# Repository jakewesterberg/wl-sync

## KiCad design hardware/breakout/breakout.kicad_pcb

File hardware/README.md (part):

# wl-sync breakout PCB

KiCad sources for the sync-box breakout board: a 2U rack-mount mixed-signal hub that sits
between the behavioural task PC, the sync-box module, the recording NI card, and the Intan RHS
amplifier. Every signal that crosses between those devices terminates on this board, is
conditioned once, and is fanned out — so a rig is reproducible from the board rather than from
hand wiring. "Sync-box module" is deliberately not a single product name: the module carries a
BCM2712 SoC and RP1 I/O controller either way, so its GPIO map and pinout are identical whether
it ships as a Raspberry Pi 5 or as a Compute Module 5 (Lite) on the official CM5 IO Board — the
choice between the two is a floorplan/placement decision this repository's own sources do not
yet lock in, not an electrical one.

Full design rationale, the signal contract, the grounding scheme, and the fabrication schedule
live in [`docs/superpowers/specs/2026-08-13-syncbox-breakout-pcb-design.md`](../docs/superpowers/specs/2026-08-13-syncbox-breakout-pcb-design.md).
The implementation plan (task breakdown, net naming convention, file layout) is at
[`docs/superpowers/plans/2026-08-13-breakout-pcb.md`](../docs/superpowers/plans/2026-08-13-breakout-pcb.md).
This repository is public: documentation here states electrical and mechanical facts and
tooling instructions only, and reproduces no text from either linked document's private source
material.

## Settled facts (record kept here, 2026-08-15)

Three facts a rig operator or firmware author needs and should not have to re-derive from the
schematic or the private spec:

- **The two photodiode comparator channels have distinct, fixed roles.** `A_PD1` watches the
  **task patch** — the stimulus-onset signal a behavioural task draws to cue an event.
  `A_PD2` watches the **flip patch**, a corner region of the display that alternates every
  refresh, making it a frame clock. Both reach the recorders as a digital edge through their
  own comparator (`PD1_COMP`/`PD2_COMP`) as well as an analog copy; the comparator lines carry
  the timing, the analog copies carry waveform and intensity.
- **The default eight analog channels Intan receives** (of the 16 sources this board carries;
  Intan's own ceiling is 8, and which eight is a mux setting, not a copper fact — see the
  ADG1206 mux truth table below): `A_PD1`, `A_EYE_LX`, `A_EYE_LY`, `A_EYE_LP`, `A_JOY_X`,
  `A_JOY_Y`, `A_MIC`, `A_ACC`. One complete eye (left, position + pupil) rather than partial
  data from both; the six eye channels are the first candidates to drop if a different set is
  ever needed, since they have an authoritative record on the eye-tracker PC independent of
  this board — the photodiode, joystick, accelerometer, and microphone channels do not.
- **MonkeyLogic's `RewardPolarity` setting must be `HIGH` to match this board.** This board's
  reward-commanded input (`RWD_CMD`) is active-HIGH by design (idle-LOW, pulses HIGH on
  delivery — the same convention every other event line on this board uses, and the polarity
  the reward-OR gate's own same-polarity structural check assumes and enforces on the
  debounced-button side). `RewardPolarity` is a MonkeyLogic Main Menu setting provided so a
  rig can match relays that trigger on sinking instead — it is a configuration to set for this
  board, never an unknown to discover at commissioning time.

## Two tracks

- **`hardware/mule/`** — the event-path mule. A small, fast board carrying only the 17-line
  event-code path plus one instance of each level-shift and isolation stage the full board
  reuses. It exists to reach the bench while the breakout board is still in layout, so the
  level-shifting and optocoupler topology gets validated against real hardware early enough to
  revise the sheets that depend on it.
- **`hardware/breakout/`** — the breakout board itself. A root sheet plus one hierarchical sheet
  per functional block (power, task-PC digital, Pi interface, analog front end, analog-to-NI,
  mux-to-Intan, comparators, opto-to-NI, opto-to-Intan, USB/I²C control).

**To route the breakout board, start at `hardware/breakout/routing-brief.md`** (2026-11-21).
The placement is generated and merged, and the brief is the handoff to the person who
routes it: what to open, what must not move, the net classes, the order to route in, the
rules by ID, the checks afterwards and what is still open. It cites the documents below
and changes none of their rules.

**Before laying out the breakout board, read `hardware/breakout/constraints.md`.** It is the
layout constraint set for plan Task 14: ground domains and the four net ties, the isolation
barriers and their slot margins, net classes, sensitive-net placement, keep-outs and the
connector faces. Every rule in it cites its source or is marked as engineering judgment, and
it ends with the questions the designer still has to answer. It sits beside the documents it
draws on: `design-review.md` (the sign-off that gates layout), `parametric-audit.md`,
`panel-elevations.md`, `frame-time-inputs.md`, `line-out-and-pfi-copy.md` and
`f6-review-brief.md`.

As of this commit, `hardware/mule/` carries a generated schematic (`mule.kicad_sch`, produced
by `hardware/gen/gen_mule.py`) and a generated, placed-but-unrouted board (`mule.kicad_pcb`,
produced by `hardware/gen/gen_mule_pcb.py`) — see `hardware/mule/floorplan.md` for the
placement rationale and the constraints a router must respect. `hardware/breakout/` carries
the root sheet (`breakout.kicad_sch`, produced by `hardware/gen/gen_breakout.py`) plus two
populated child sheets so far: `sheets/power.kicad_sch` (produced by
`hardware/gen/gen_breakout_power.py`, Task 7) — the 5-position analog/logic inlet (widened
from 4 pins at Task 7 fix round 1, see below), the +3V3 logic rail regulated from +5V, and
the one isolated ±12V supply the other nine sheets draw power from; see that generator's own
module docstring and `check_breakout_power_netlist.py` for the design and its verification.
Task 7 fix round 1 (task-7-report.md's "Fix round 1") corrected two defects found in
review: the +5V rail was undersized regulating it down from +12V on board (fixed by
bringing +5V in directly from the external supply on a fifth inlet pin instead, budgeted
for 400mA), and the child sheet's own component `(instances (path ...))` ancestor chain was
self-referential rather than the real root+sheet-symbol chain a nested sheet needs (fixed
generically in `kicad_sch.py`, not just for this one sheet — see the "KiCad gotchas" entry
below). Task 7 fix round 2 (task-7-report.md's "Fix round 2") replaced the inlet
**connector** itself — not its electrical design — after a reviewer confirmed the mini-DIN
footprints modelled an evenly-spaced ring the real Same Sky MD-40SN/MD-50SN datasheet's own
diagrams contradict, and that both parts are discontinued besides. The inlet is now a
5-position, IEC 61076-2-101 A-coded, keyed, screw-locking M12 connector (Amphenol LTW
M12A-05PFFP-SF8001, current production, 811 units in stock directly confirmed at DigiKey)
— see "Custom connector footprints" below for the full selection rationale and
per-dimension sourcing.

**Panel-instrumentation task (2026-08-15), Change D — four of the five "things a rack
instrument needs that this one lacked" (spec §9.8) land on this sheet** (the fifth,
the barcode heartbeat LED, is on `pi-interface.kicad_sch` — see that sheet's own
paragraph below):

- **Chassis earth stud (`J56`):** a `Connector_Generic:Conn_01x01` on footprint
  `MountingHole:MountingHole_3.2mm_M3_Pad` — an M3-clearance hole *with* a connected
  copper pad, simultaneously the mechanical mount and the electrical land the
  cage-to-rack bond (spec §5.6) needs somewhere to terminate. Carries a new net,
  `CHASSIS_GND`, joined to `DGND` at exactly one net tie (`NT3`) — mirroring `NT2`'s own
  `FAN_RTN`↔`DGND` treatment exactly, so the stud reaches the board's single star point
  transitively (through `NT3` then `NT1`/`NT2`), never by a second, competing path.
- **Power-good LED per rail (`D40`/`D41`/`D42`, +12V/−12V/+5V):** series resistor + LED
  between each rail and its own local ground reference (`AGND` for ±12V, `DGND` for
  +5V) — `−12V`'s own pair is mirrored (resistor/anode on the `AGND` side, cathode on
  `−12V`), the identical reasoning `D2`'s own reverse-polarity-diode orientation already
  uses. ~4.5 mA target each (`R192`/`R193` = 2.2k, `R194` = 680R) — negligible against
  any rail's own real budget.
- **Rail test points (`TP1`–`TP7`):** one `Connector:TestPoint` per voltage rail (+12V,
  −12V, +5V, +3V3, ISO_P12, ISO_N12) *plus one on `INTAN_GND`* — the isolated domain's
  own reference, without which `ISO_P12`/`ISO_N12` cannot actually be measured at all
  (`INTAN_GND` is galvanically separate from `AGND`/`DGND`, spec §5.3/§5.5). `AGND`/
  `DGND` themselves are not given dedicated test points — already trivially probable at
  any of this sheet's own many ground pads.
- **Main input fusing (`F2`/`F3`/`F4`, +12V/−12V/+5V):** "the fans already have a
  polyfuse; these did not" (spec §9.8). Placed upstream of each rail's own existing
  reverse-polarity diode (`D1`/`D2`/`D3`) — their own raw-side net renamed `*_FUSED`
  (e.g. `P12_RAW` → `F2` → `P12_FUSED` → `D1` → `+12V`), `D1`–`D3` themselves keeping
  their existing references unchanged. `F2`/`F3` are Littelfuse `1206L050/15YR`
  (500 mA hold / 1 A trip / **15 V** max), the same real part as the fan feed's `F1`.

  **`F4` is a different part — finding M7, 2026-08-16.** The sizing note that used to
  sit here called +5V's 1.25× hold margin "tighter than usual but accepted, because a
  main-input fuse guards against a gross fault". That reasoning does not survive finding
  F1: the +5 V rail now carries **392 mA typ / 495 mA max**, and a `1206L050` holds only
  ~0.44 A at this chassis's 35 °C ambient. It would have tripped in **normal operation**,
  not on a fault. `F4` is now **`1206L110-C`** — 1.10 A hold / 2.20 A trip, ~0.97 A
  derated at 35 °C, a 1.97× margin.

  **Its V_max is 6 Vdc, not 15, and that is not interchangeable.** In the 1206L series
  the elevated-voltage variants exist only at the two lowest hold currents; everything at
  0.75 A and above is a +5 V-rail part. So `F4` could move and `F1`/`F2`/`F3` cannot —
  **0.50 A is the largest 1206L hold current available to a 12 V rail at all**, which is
  also why M7's "0.75 A recommended" for the fan feed cannot be satisfied in this series.
  Do not consolidate the two values back into one.

- **The fan branch is parallel to the main +12 V branch, not downstream of it (finding
  F7, 2026-08-16).** `F1` used to be fed from `+12V`, which put it in series with `F2` at
  identical ratings — and two identical parts in series have no selectivity at all: a fan
  fault at 0.9 A is below `F1`'s trip but over `F2`'s hold, so **`F2` could open first and
  kill the analog rails to protect the fans.** The fan feed now taps `P12_RAW` directly,
  with its own reverse-polarity Schottky (`D44`, `SS14`) since it no longer sits behind
  `D1`:

  ```
  J1.1 → P12_RAW ─┬─ [F2] → P12_FUSED   → [D1]  → +12V      (main, 97–121 mA)
                  └─ [F1] → FAN_12V_RAW → [D44] → FAN_12V   (fans, 240 mA)
  ```

- **Every panel output now sits behind series resistance, and no logic output drives more
  than one connector (findings F4 and M3, 2026-08-16).** `CAM_TRIG_BEH` drove **four** BNCs
  from a single `SN74AHCT541` output: four parallel coax runs present Z₀/4 ≈ 12.5 Ω, so the
  initial edge drew roughly **118 mA against the part's 25 mA per-output absolute
  maximum** — brief, but on every edge for the life of the board, and with no source
  termination the cameras could see reflections and double-trigger. Each trigger now has its
  own buffer channel (`CAM_TRIG_BEH1`–`4`, the extra three on `U74`) and its own **47 Ω**.
  They still share one trigger *rate* via `CAM_TRIG_BEH_RAW`; they no longer share a driver.

  M3 named **six** bare panel outputs. There were **eleven** — the five *digital* Intan
  output BNCs sat directly on the ACSL-6xx0 output pins too. (The finding's "every Intan
  output has a series resistor" is true of the *analog* outputs, which each sit behind
  100 Ω, and was not true of the digital ones.) All eleven now carry series resistance:
  47 Ω on the five camera triggers, 100 Ω on `J6` and the five Intan BNCs. The extra five
  were found by the checker written *for* M3, which is stated over every panel output rather
  than over the six nets the finding lists.

  `tests/hardware/test_netlist.py` derives series-ness from **topology** — by testing
  whether removing one fuse disconnects another from the supply inlet — rather than from
  net names. That matters: the audit's own published fix for this named `P12_FUSED` as
  "upstream of `F2`" when it is `F2`'s *output*, which would have fixed nothing and
  removed the fan branch's reverse-polarity protection as well. ±12V's own real total draw was **not** independently characterized
  to the same precision (it sums a computed IH1215D input-current estimate, the fan
  feed, and an uncharacterized contribution from the ±12V-referenced op-amp stages on
  `analog-frontend.kicad_sch`/`analog-ni.kicad_sch`) — flagged explicitly for bench
  confirmation before treating the margin as final, the same "tell me if it doesn't fit"
  posture this file's own +3V3/NI-budget notes already use elsewhere. A higher-current,
  higher-voltage PPTC (Bourns `MF-SM` series) was evaluated and **rejected**: its own
  datasheet states hand soldering is not recommended, which would add a third accepted
  hand-solderability exception beyond the two spec §10.1 documents (`MCP4728`, the two
  exposed-pad regulators) — see `_place_inlet()`'s own docstring for the full account.

And `sheets/taskpc-digital.kicad_sch` (produced by
`hardware/gen/gen_breakout_taskpc_digital.py`, Task 8) — both task-PC MDR68 connectors
(Connector 1 wired with the 23 digital lines; Connector 0 carries its 9 task-PC analog
channels plus the AISENSE-to-AGND tie, everything else no_connect pending Task 10's own
front-end/buffer circuitry), the 19-channel inbound protected/buffered path (100Ω +
BAT54S clamp per channel, high side +5V never +3V3, fanned out in parallel to a 3.3V
`SN74LVC541APW` bank and a 5V `SN74AHCT541PW` `_BUF` bank for Task 11's optocouplers), the
4-channel outbound path, and the reward OR (`74HCT32` + a single debounced `74HCT14`
Schmitt inverter); see that generator's own module docstring and
`check_taskpc_digital_netlist.py` for the design and its verification. Task 8 is this
project's first case of two REAL sibling child sheets coexisting, which surfaced a
cross-sheet reference-collision gotcha `kicad_sch.py` needed a generic fix for — see the
"KiCad gotchas" entry below.

**Task 8 fix round 1** (`task-8-report.md`'s own "Fix round 1") corrected three findings
raised by the implementer's own report, all disclosed concerns the implementer was right
to flag: (1) **critical** — the reward-OR debounce stage placed a `74HCT14` Schmitt
*pair* (task-8-brief.md's own literal, incorrect text); two series inversions cancel, so
the debounced button would idle HIGH into an OR gate against an active-HIGH `RWD_CMD`,
asserting `RWD_DLVR` continuously. Fixed to a *single* inverter (idle-LOW/active-HIGH,
matching an OR gate's actual requirement); `RWD_CMD`'s assumed active-HIGH polarity is
now stated explicitly on-sheet, and the checker asserts the OR's two inputs are
same-polarity. (2) Connector 1's physical MDR68 pin assignment was this sheet's own
sequential guess; it is now sourced from NI's own "X Series User Manual" (National
Instruments 370784K-01, May 2019), Figure A-5 "NI PCIe-6323/6343 Pinout" — the task PC's
own card — for every P0.x and D GND position. (3) Connector 0's 9 task-PC analog channels
(`A_EYE_LX_TPC` etc., plan.md's own net-naming table) and its AISENSE-to-AGND tie are now
wired on this sheet (the same physical-pin source above), since only the file that places
a symbol can label its pins and Task 10 does not exist yet. See `task-8-report.md`'s own
"Fix round 1" section for the full retrieval/verification method and the reasoning behind
each fix.

**Panel-instrumentation task (2026-08-15), Changes A+B — manual reward becomes a one-shot,
and the three reward positions become real connectors.** Both changes land entirely on
`taskpc-digital.kicad_sch`'s own reward circuit:

- **One-shot (Change A):** a Nexperia `74HCT123D` dual retriggerable monostable (`U69`)
  now sits between the debounce inverter's own output (`RWD_BTN_DEB`) and the reward-OR
  gate's second input (`RWD_BTN_PULSE`, the one-shot's own `Q`) — every hand-delivered
  reward gets a fixed **~199 ms** pulse regardless of how long the button is held (spec
  §3.1). `Rext=442k` (E96) + `Cext=1µF` (`R191`/`C149`, both minted out of band), K=0.45 at
  VCC=5.0V (the part's own datasheet, Table 10) → tW = 0.45×442×1,000,000 ns ≈ 198.9 ms,
  cross-checked against that same table's own measured example (100 nF/10 kΩ → 450 µs;
  the formula predicts exactly that). Real part, not TI: TI's own `CD74HCT123M`/`MT` is
  obsolete; Nexperia's `74HCT123D` is current production, thousands of units in stock at
  DigiKey/Mouser/TME (checked 2026-08-15). Pin map verified pin-by-pin against
  Philips/Nexperia's own Rev. 03 (11 May 2004) datasheet, Table 3/Fig. 5, cross-checked
  against KiCad's own stock `74xx:74HCT123` library entry — see
  `gen_breakout_taskpc_digital.py`'s own `place_reward_oneshot()` docstring for the full
  account, including why the part's own retriggerable behaviour does not undermine "fixed
  duration regardless of hold time" (a continuous hold produces exactly one trigger edge).
  The debounce capacitor changes from 100 nF to **1 µF** (10 kΩ × 1 µF = 10 ms, spec
  §3.1), covering both switch bounce and the longer remote-BNC cable run's own
  connector-mating transient.
- **Real connectors (Change B):** the manual reward button (`J4`) is now
  `Switch:SW_Push` on a real panel/chassis-mount momentary-pushbutton footprint
  (`Button_Switch_THT:SW_PUSH-12mm`), **recessed** per spec §3.1 ("so a sleeve or cable
  cannot dispense fluid"). The remote reward jack (`J5`) and reward-driver output (`J6`)
  are both real BNCs (`Connector:Conn_Coaxial` / `Connector_Coaxial:BNC_PanelMountable_
  Vertical` — the same footprint the camera-trigger BNCs already use), replacing generic
  `Connector_Generic:Conn_01x02` placeholders. **This removes the 3.5 mm TRS from the
  design entirely** — `J5` was its last use (spec §9.6): a BNC's own center pin cannot
  transiently short to the shield while mating the way a TRS tip/ring/sleeve does sliding
  past a jack's own switching contacts, so plugging in the handheld remote cannot itself
  fire a reward, and the coupling locks. No TRS footprint or symbol exists anywhere on the
  board any more (confirmed by grep across every generator and committed sheet, and
  asserted directly by `check_taskpc_digital_netlist.py`'s own whole-board footprint scan,
  with a negative control). `J4`/`J5`/`J6` keep their existing reference numbers — the
  symbol/footprint/value changed at their own existing call sites, nothing moved.

**A real ref_start hazard, found and fixed while making these changes, not before:**
`taskpc-digital.kicad_sch`'s own `build()` used to re-derive its reference-counter seed by
reading `power.kicad_sch`'s *current* committed text on every regeneration
(`find_max_refs(POWER_SCH.read_text())`). That was safe until power.kicad_sch's own
fan-header addendum (spec §9.5) minted `J52`–`J55`/`C147`/`C148` out of band, *after*
taskpc-digital.kicad_sch was last generated — from that point on, simply regenerating
taskpc-digital.kicad_sch again (even with no source changes at all) would have silently
**renumbered every one of its own existing J- and C-prefixed components**, since the
recomputed seed jumps from the sheet's own small pre-fan-header baseline straight to
power.kicad_sch's own new, much larger maxima. Confirmed empirically before fixing it: an
unmodified copy of the generator, run against the *current* power.kicad_sch, reproduced
`R24`/`D22`/`U13` exactly (genuinely unaffected) but `J60`/`C158` instead of the
historically-correct `J6`/`C31`. Fixed by **pinning** `ref_start` to the exact historical
values instead of re-deriving them live — see `gen_breakout_taskpc_digital.py`'s and
`gen_breakout_pi_interface.py`'s own `build()` docstrings (the latter has the identical
fix, for the identical reason: it also seeds from power.kicad_sch, plus this same
taskpc-digital.kicad_sch). **The lesson for every future out-of-band addition to an
already-depended-upon sheet:** it silently sets a trap for every downstream sibling's own
next regeneration, not just an inconvenience for the sheet being edited — check every
sibling that reads the changed file's maxima, not only the file itself.
And `sheets/pi-interface.kicad_sch` (produced by `hardware/gen/gen_breakout_pi_interface.py`,
Task 9) — the sync-module (Raspberry Pi 5 / Compute Module 5 IO Board, see this file's own
opening paragraph) 40-pin GPIO header, wired to spec Sec.4's own GPIO map (transcribed
verbatim as an on-sheet text block); the GPIO0/GPIO1 boot-contention 330Ω series resistors;
a `SN74AHCT541PW` output buffer for the three module-sourced signals this sheet produces
(`BARCODE_PI` fanned to 5 placeholder/spare panel headers, plus `BARCODE_BUF`/
`BARCODE_INTAN_BUF` on two more channels of the same package, one optocoupler LED each;
`CAM_TRIG_EYE`/`CAM_TRIG_BEH` fanned to 5 real panel BNC positions, 1 eye + 4 behavior);
and the internal
2.54mm 1×4 USB header for Task 12's own USB-I²C bridge. Also, NOT in the brief's own literal
step list: one more `SN74LVC541APW` channel on +3V3, level-shifting `RWD_DLVR` — produced on
`taskpc-digital.kicad_sch` by a `74HCT32` OR gate powered from **+5V** — down to a
module-safe level before it reaches GPIO23. This project's own global constraint (the plan's
own "Pi GPIO is 3.3V and not 5V tolerant... never one part for both") makes wiring `RWD_DLVR`
to GPIO23 directly a real hazard, not a style nit — the same class of catch-and-fix-beyond-
the-literal-brief Task 8 fix round 1 already made for its own reward-OR polarity defect (see
above), applied here to a defect that never made it into a committed sheet in the first
place. See that generator's own module docstring and
`check_breakout_pi_interface_netlist.py` for the design and its verification — including the
GPIO-physical-pin walk (independently re-derived, not imported from the generator) this
task's own brief specifically asked for, with a negative control that moves one GPIO signal
to a wrong pin and confirms the checker fires (this defect class is invisible to ERC: a
transposed physical pin is still a fully-connected, 0-error netlist, and only fails on a
bench during PIO capture bring-up).

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
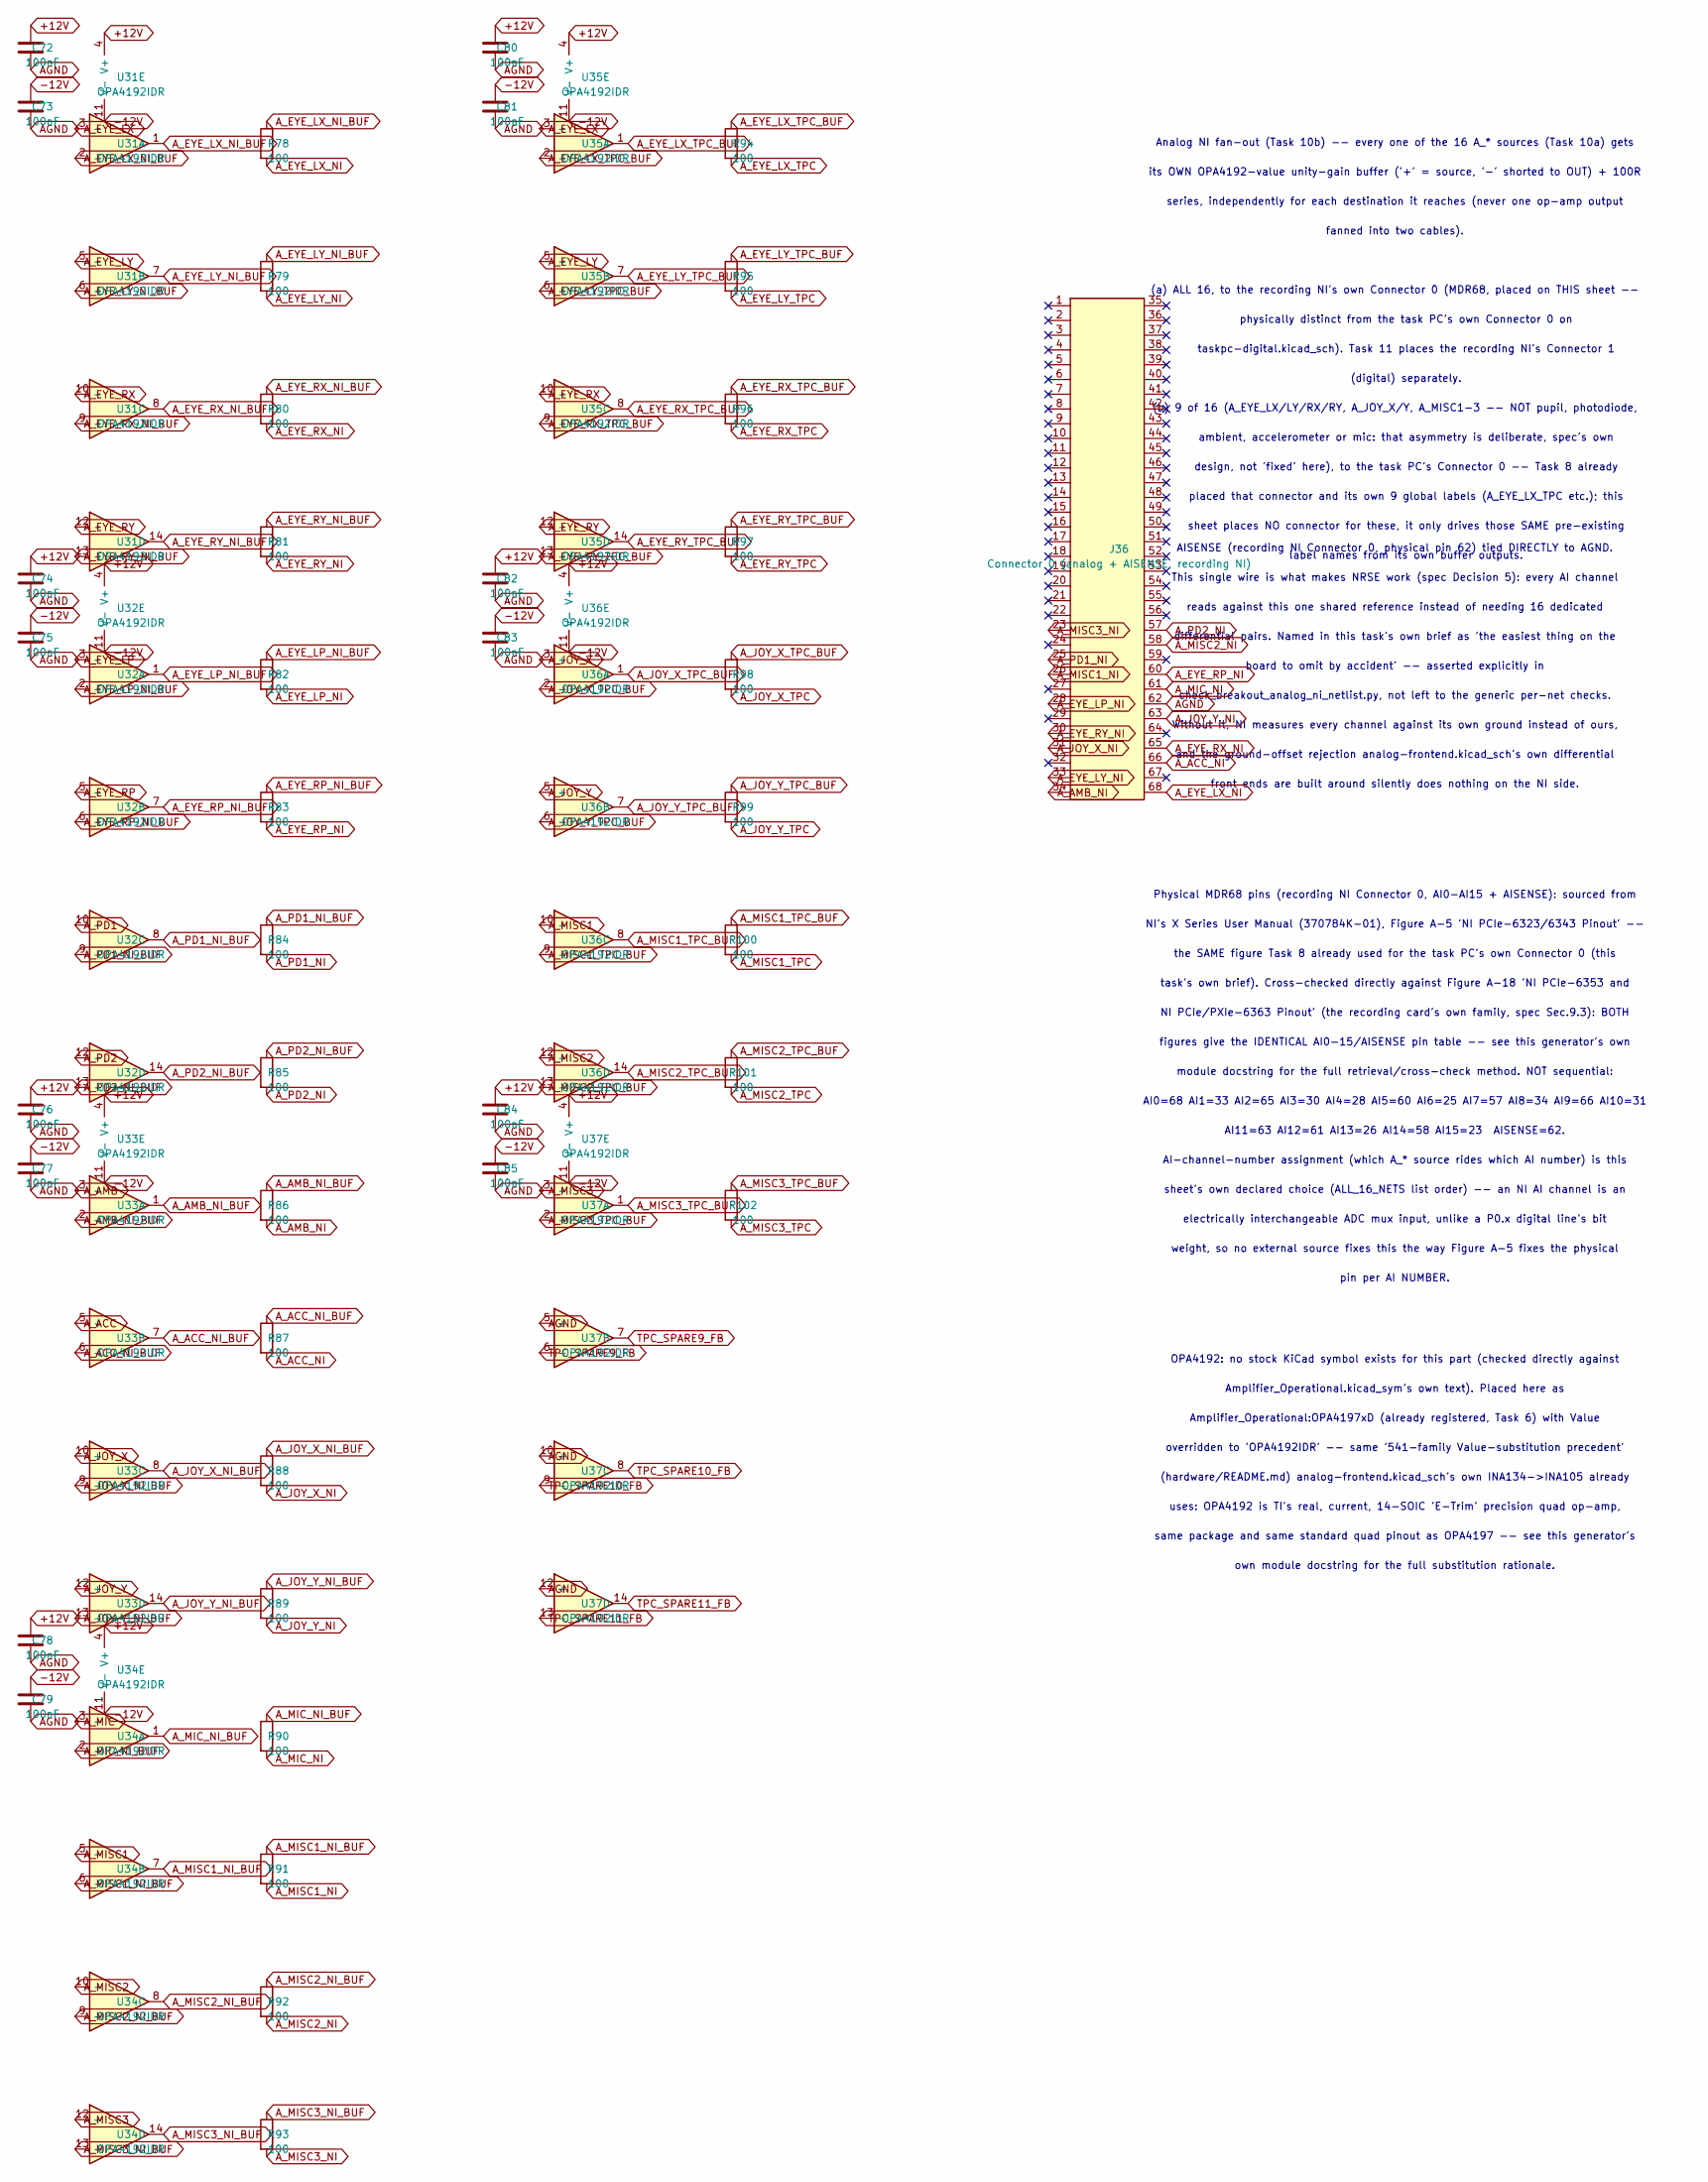
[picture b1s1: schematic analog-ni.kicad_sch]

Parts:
C72, C73, C74, C75, C76, C77, C78, C79, C80, C81, C82, C83, C84, C85: 100nF; C_0603_1608Metric
J36: Connector 0 (analog + AISENSE, recording NI); MDR68_Male_RightAngle
R78, R79, R80, R81, R82, R83, R84, R85, R86, R87, R88, R89, R90, R91, R92, R93, R94, R95, R96, R97, R98, R99, R100, R101, R102: 100; R_0603_1608Metric
U31, U32, U33, U34, U35, U36, U37: OPA4192IDR; SOIC-14_3.9x8.7mm_P1.27mm

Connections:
A_ACC: U33.5 (+); also elsewhere on the board
A_ACC_NI: J36.66, R87.2
A_ACC_NI_BUF: R87.1, U33.6 (-), U33.7
A_AMB: U33.3 (+); also elsewhere on the board
A_AMB_NI: J36.34, R86.2
A_AMB_NI_BUF: R86.1, U33.1, U33.2 (-)
A_EYE_LP: U32.3 (+); also elsewhere on the board
A_EYE_LP_NI: J36.28, R82.2
A_EYE_LP_NI_BUF: R82.1, U32.1, U32.2 (-)
A_EYE_LX: U31.3 (+), U35.3 (+); also elsewhere on the board
A_EYE_LX_NI: J36.68, R78.2
A_EYE_LX_NI_BUF: R78.1, U31.1, U31.2 (-)
A_EYE_LX_TPC: R94.2; also elsewhere on the board
A_EYE_LX_TPC_BUF: R94.1, U35.1, U35.2 (-)
A_EYE_LY: U31.5 (+), U35.5 (+); also elsewhere on the board
A_EYE_LY_NI: J36.33, R79.2
A_EYE_LY_NI_BUF: R79.1, U31.6 (-), U31.7
A_EYE_LY_TPC: R95.2; also elsewhere on the board
A_EYE_LY_TPC_BUF: R95.1, U35.6 (-), U35.7
A_EYE_RP: U32.5 (+); also elsewhere on the board
A_EYE_RP_NI: J36.60, R83.2
A_EYE_RP_NI_BUF: R83.1, U32.6 (-), U32.7
A_EYE_RX: U31.10 (+), U35.10 (+); also elsewhere on the board
A_EYE_RX_NI: J36.65, R80.2
A_EYE_RX_NI_BUF: R80.1, U31.8, U31.9 (-)
A_EYE_RX_TPC: R96.2; also elsewhere on the board
A_EYE_RX_TPC_BUF: R96.1, U35.8, U35.9 (-)
A_EYE_RY: U31.12 (+), U35.12 (+); also elsewhere on the board
A_EYE_RY_NI: J36.30, R81.2
A_EYE_RY_NI_BUF: R81.1, U31.13 (-), U31.14
A_EYE_RY_TPC: R97.2; also elsewhere on the board
A_EYE_RY_TPC_BUF: R97.1, U35.13 (-), U35.14
A_JOY_X: U33.10 (+), U36.3 (+); also elsewhere on the board
A_JOY_X_NI: J36.31, R88.2
A_JOY_X_NI_BUF: R88.1, U33.8, U33.9 (-)
A_JOY_X_TPC: R98.2; also elsewhere on the board
A_JOY_X_TPC_BUF: R98.1, U36.1, U36.2 (-)
A_JOY_Y: U33.12 (+), U36.5 (+); also elsewhere on the board
A_JOY_Y_NI: J36.63, R89.2
A_JOY_Y_NI_BUF: R89.1, U33.13 (-), U33.14
A_JOY_Y_TPC: R99.2; also elsewhere on the board
A_JOY_Y_TPC_BUF: R99.1, U36.6 (-), U36.7
A_MIC: U34.3 (+); also elsewhere on the board
A_MIC_NI: J36.61, R90.2
A_MIC_NI_BUF: R90.1, U34.1, U34.2 (-)
A_MISC1: U34.5 (+), U36.10 (+); also elsewhere on the board
A_MISC1_NI: J36.26, R91.2
A_MISC1_NI_BUF: R91.1, U34.6 (-), U34.7
A_MISC1_TPC: R100.2; also elsewhere on the board
A_MISC1_TPC_BUF: R100.1, U36.8, U36.9 (-)
A_MISC2: U34.10 (+), U36.12 (+); also elsewhere on the board
A_MISC2_NI: J36.58, R92.2
A_MISC2_NI_BUF: R92.1, U34.8, U34.9 (-)
A_MISC2_TPC: R101.2; also elsewhere on the board
A_MISC2_TPC_BUF: R101.1, U36.13 (-), U36.14
A_MISC3: U34.12 (+), U37.3 (+); also elsewhere on the board
A_MISC3_NI: J36.23, R93.2
A_MISC3_NI_BUF: R93.1, U34.13 (-), U34.14
A_MISC3_TPC: R102.2; also elsewhere on the board
A_MISC3_TPC_BUF: R102.1, U37.1, U37.2 (-)
A_PD1: U32.10 (+); also elsewhere on the board
A_PD1_NI: J36.25, R84.2
A_PD1_NI_BUF: R84.1, U32.8, U32.9 (-); also elsewhere on the board
A_PD2: U32.12 (+); also elsewhere on the board
A_PD2_NI: J36.57, R85.2
A_PD2_NI_BUF: R85.1, U32.13 (-), U32.14; also elsewhere on the board
TPC_SPARE9_FB: U37.6 (-), U37.7
TPC_SPARE10_FB: U37.8, U37.9 (-)
TPC_SPARE11_FB: U37.13 (-), U37.14

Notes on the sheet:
Analog NI fan-out (Task 10b) -- every one of the 16 A_* sources (Task 10a) gets
its OWN OPA4192-value unity-gain buffer ('+' = source, '-' shorted to OUT) + 100R
series, independently for each destination it reaches (never one op-amp output
fanned into two cables).
(a) ALL 16, to the recording NI's own Connector 0 (MDR68, placed on THIS sheet --
physically distinct from the task PC's own Connector 0 on
taskpc-digital.kicad_sch). Task 11 places the recording NI's Connector 1
(digital) separately.
(b) 9 of 16 (A_EYE_LX/LY/RX/RY, A_JOY_X/Y, A_MISC1-3 -- NOT pupil, photodiode,
ambient, accelerometer or mic: that asymmetry is deliberate, spec's own
design, not 'fixed' here), to the task PC's Connector 0 -- Task 8 already
placed that connector and its own 9 global labels (A_EYE_LX_TPC etc.); this
sheet places NO connector for these, it only drives those SAME pre-existing
label names from its own buffer outputs.
AISENSE (recording NI Connector 0, physical pin 62) tied DIRECTLY to AGND.
This single wire is what makes NRSE work (spec Decision 5): every AI channel
reads against this one shared reference instead of needing 16 dedicated
differential pairs. Named in this task's own brief as 'the easiest thing on the
board to omit by accident' -- asserted explicitly in
check_breakout_analog_ni_netlist.py, not left to the generic per-net checks.
Without it, NI measures every channel against its own ground instead of ours,
and the ground-offset rejection analog-frontend.kicad_sch's own differential
front ends are built around silently does nothing on the NI side.
Physical MDR68 pins (recording NI Connector 0, AI0-AI15 + AISENSE): sourced from
NI's X Series User Manual (370784K-01), Figure A-5 'NI PCIe-6323/6343 Pinout' --
the SAME figure Task 8 already used for the task PC's own Connector 0 (this
task's own brief). Cross-checked directly against Figure A-18 'NI PCIe-6353 and
NI PCIe/PXIe-6363 Pinout' (the recording card's own family, spec Sec.9.3): BOTH
figures give the IDENTICAL AI0-15/AISENSE pin table -- see this generator's own
module docstring for the full retrieval/cross-check method. NOT sequential:
AI0=68 AI1=33 AI2=65 AI3=30 AI4=28 AI5=60 AI6=25 AI7=57 AI8=34 AI9=66 AI10=31
AI11=63 AI12=61 AI13=26 AI14=58 AI15=23 AISENSE=62.
AI-channel-number assignment (which A_* source rides which AI number) is this
sheet's own declared choice (ALL_16_NETS list order) -- an NI AI channel is an
electrically interchangeable ADC mux input, unlike a P0.x digital line's bit
weight, so no external source fixes this the way Figure A-5 fixes the physical
pin per AI NUMBER.
OPA4192: no stock KiCad symbol exists for this part (checked directly against
Amplifier_Operational.kicad_sym's own text). Placed here as
Amplifier_Operational:OPA4197xD (already registered, Task 6) with Value

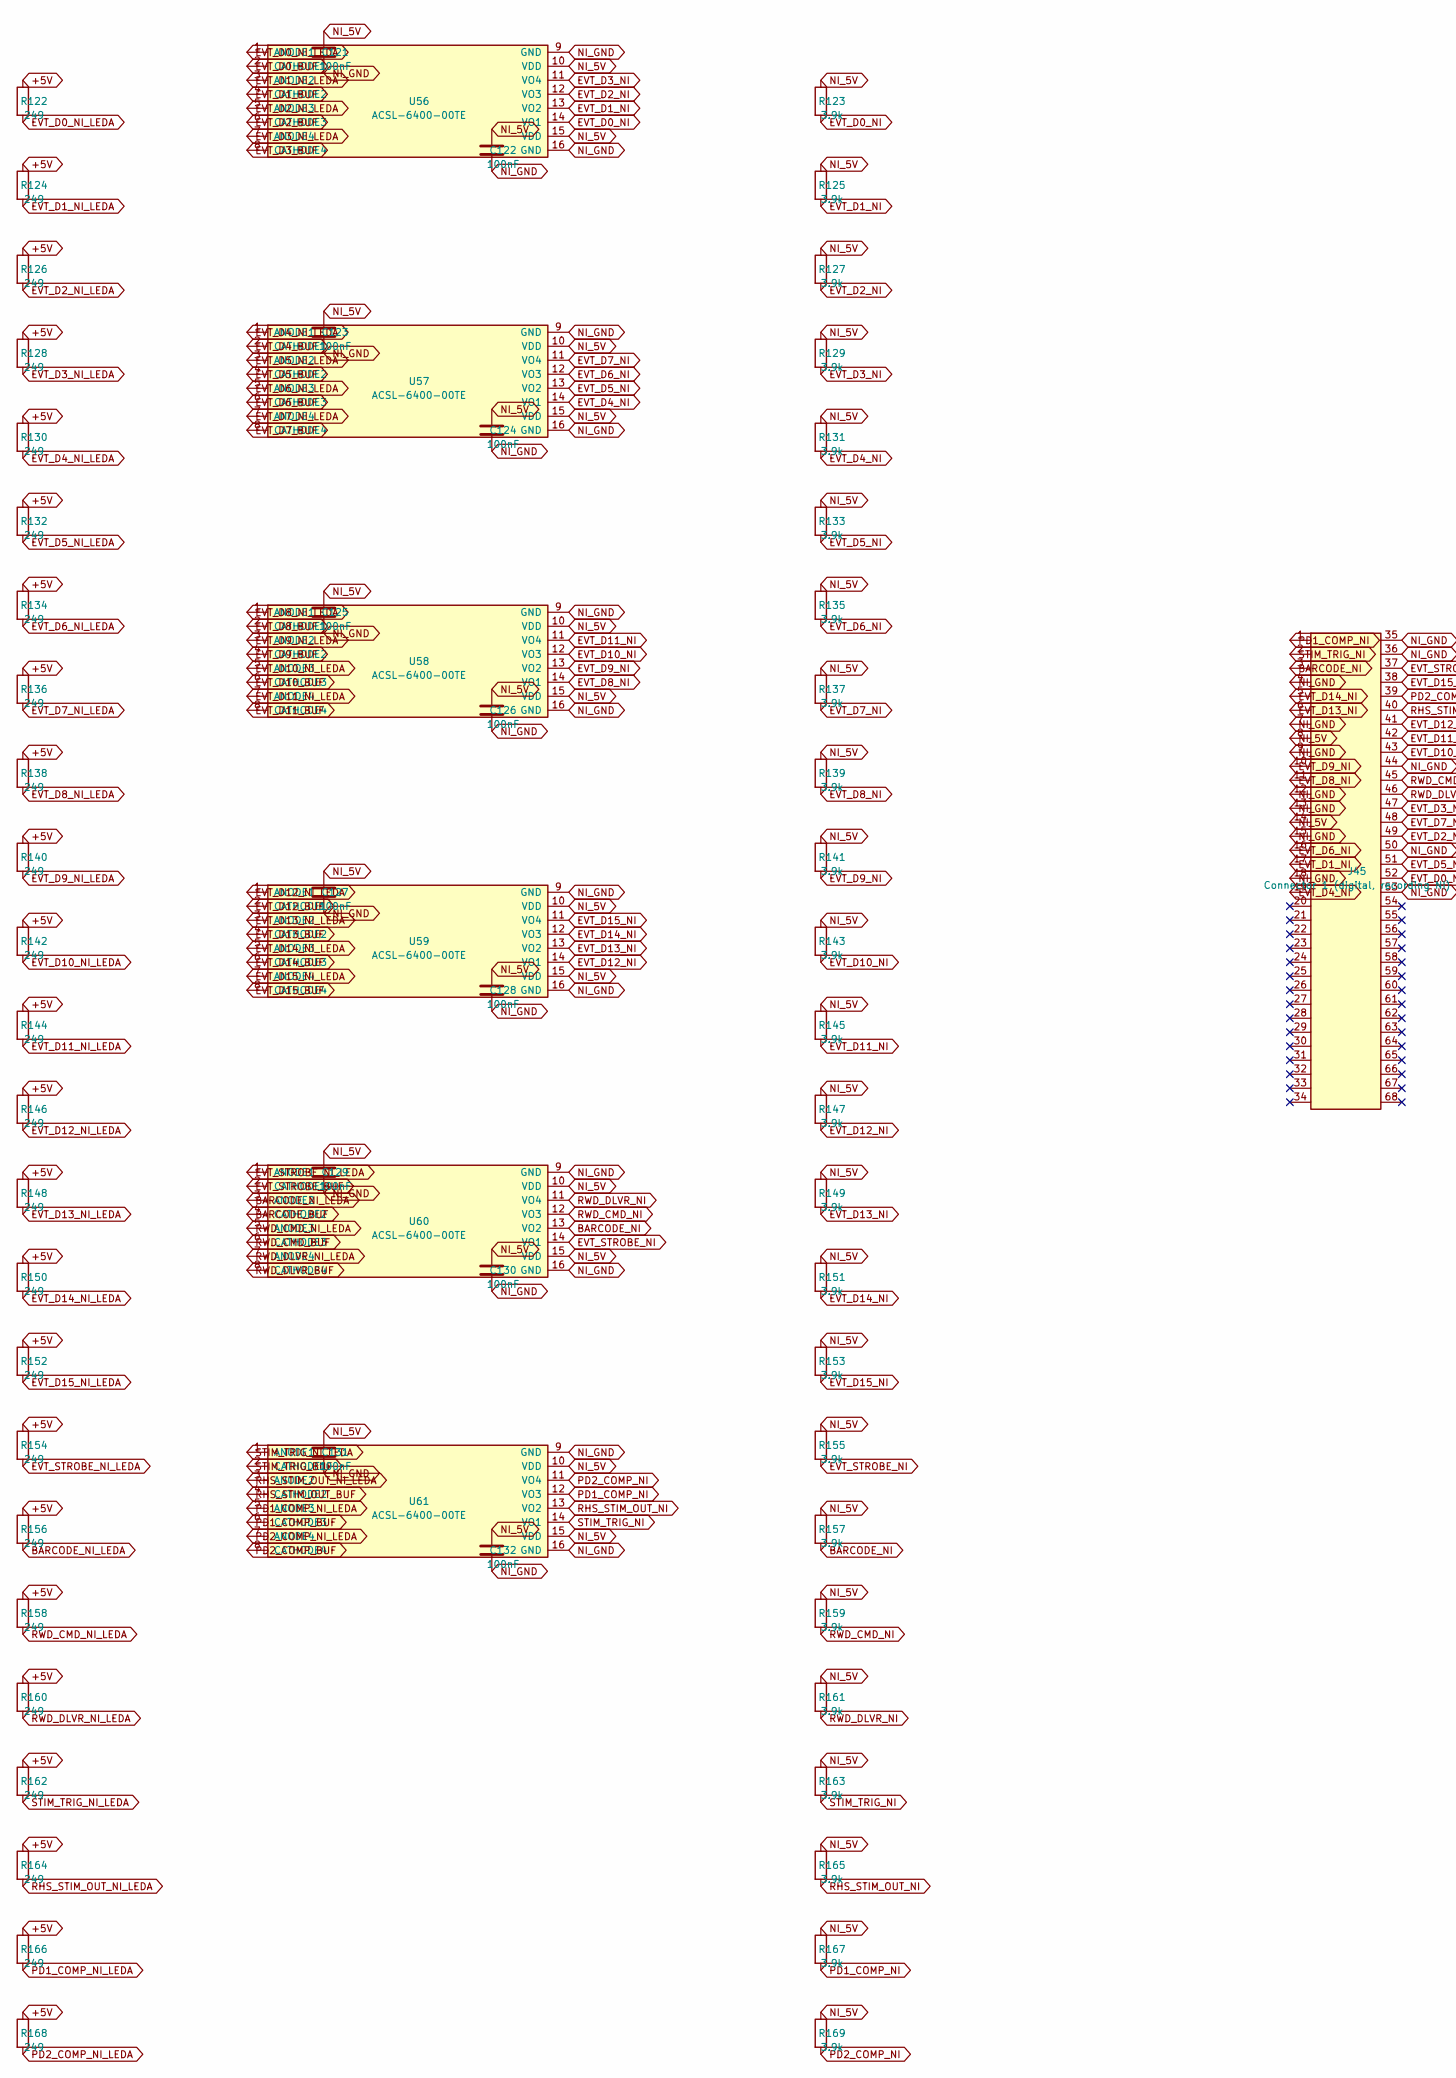
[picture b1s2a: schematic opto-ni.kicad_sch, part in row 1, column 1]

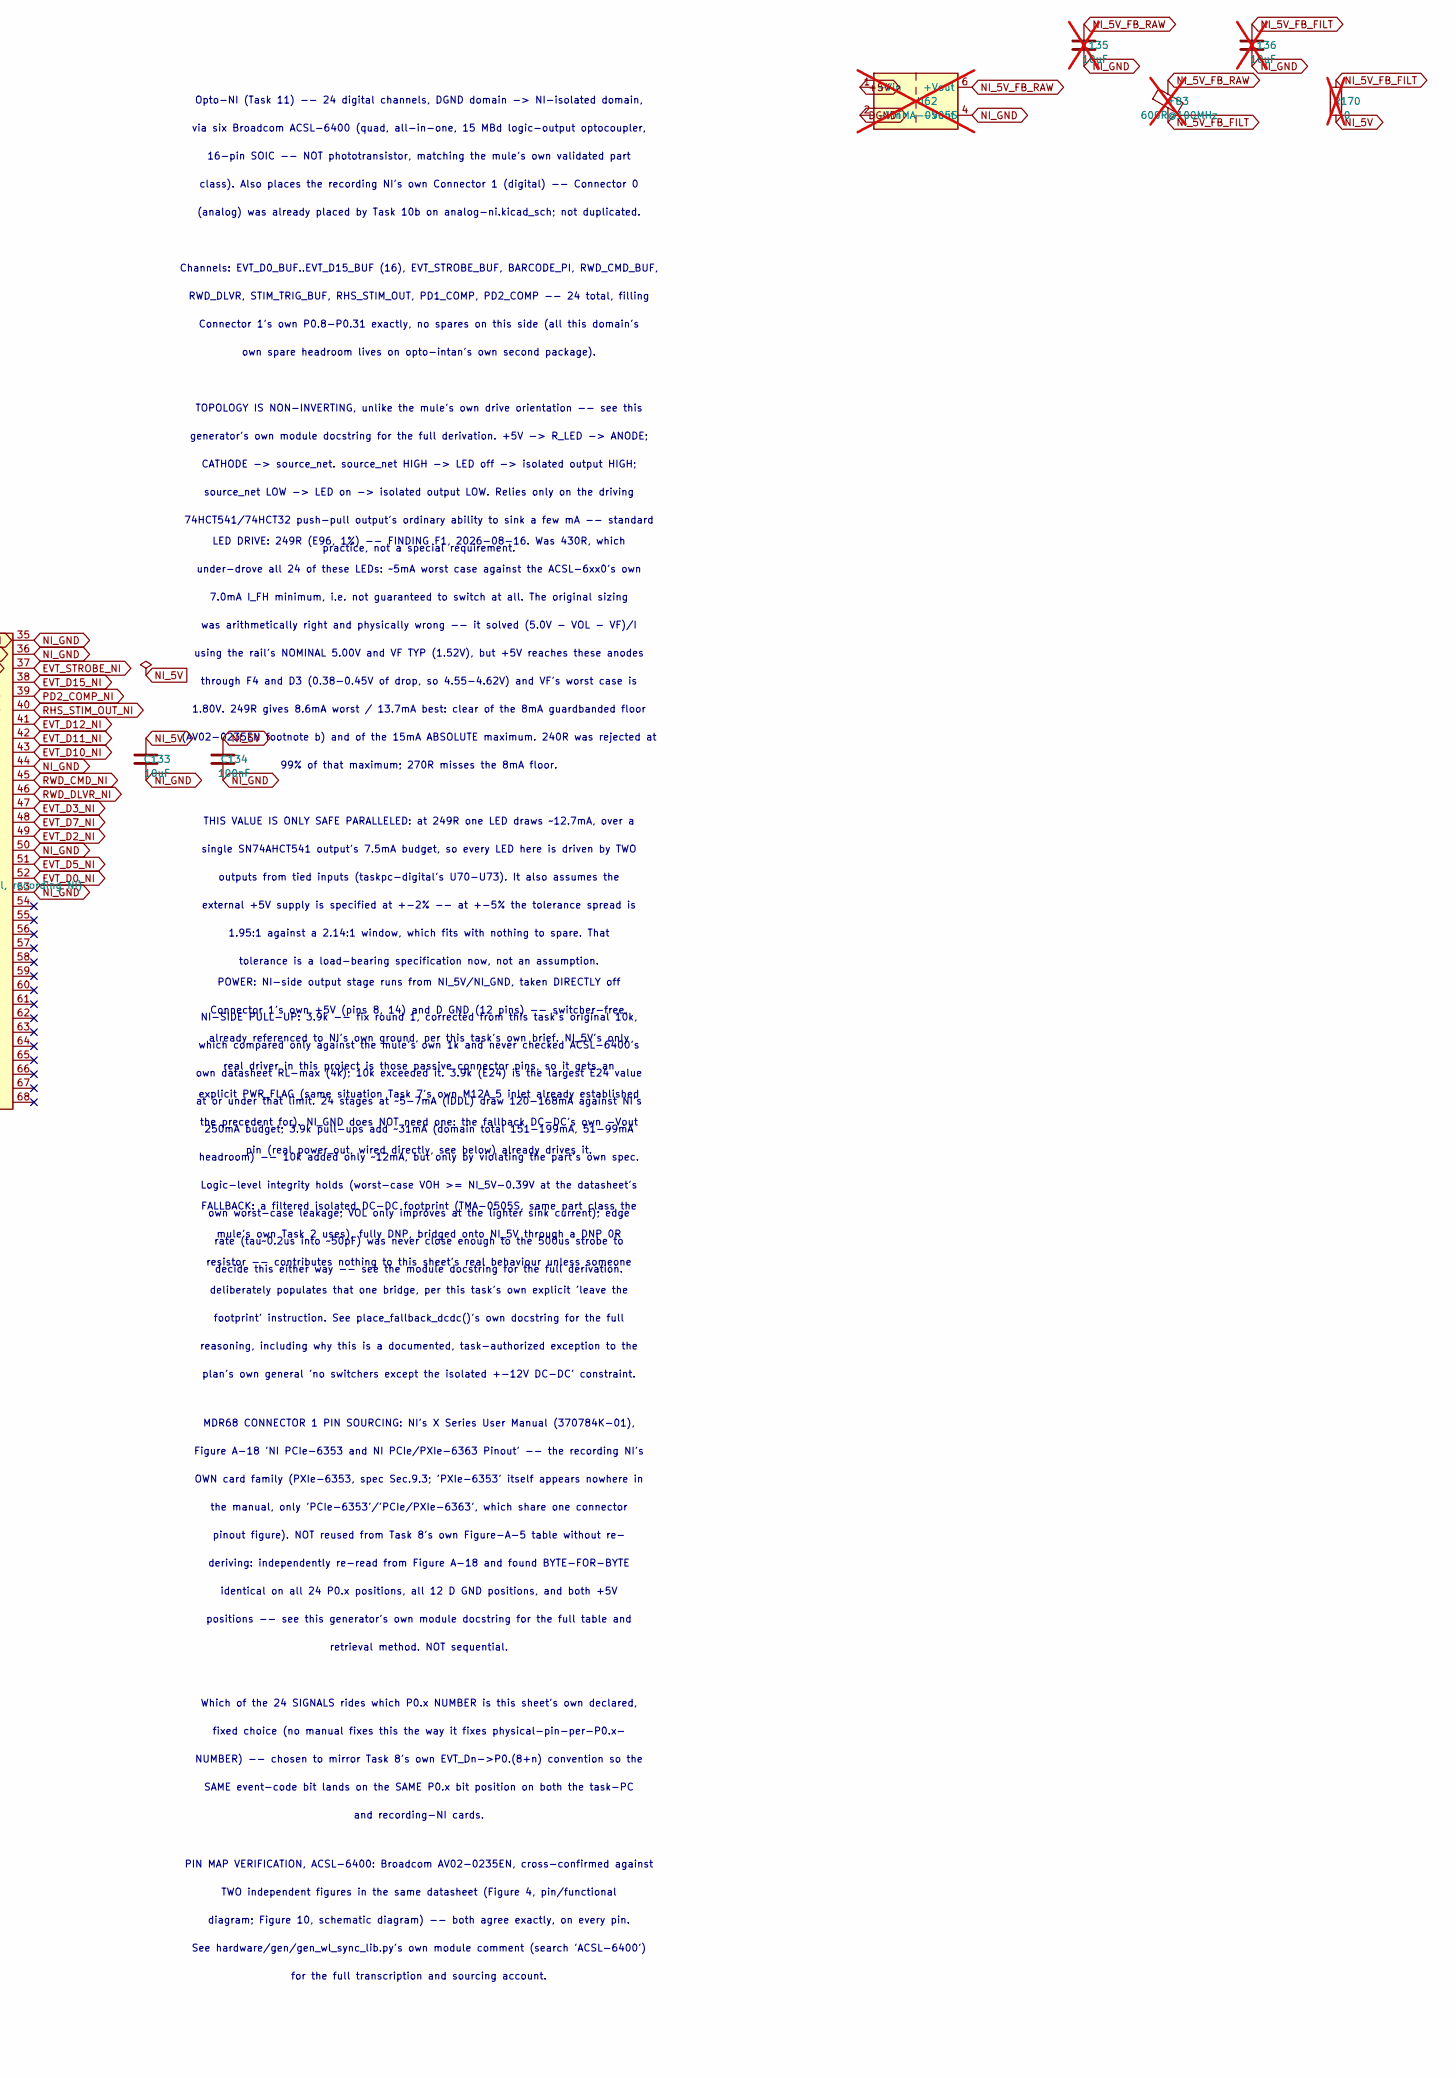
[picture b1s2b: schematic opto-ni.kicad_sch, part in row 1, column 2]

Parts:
C121, C122, C123, C124, C125, C126, C127, C128, C129, C130, C131, C132, C134: 100nF; C_0603_1608Metric
C133: 10uF; C_1206_3216Metric
C135, C136: 10uF; C_1206_3216Metric; not fitted
FB3: 600R@100MHz; L_0805_2012Metric; not fitted
J45: Connector 1 (digital, recording NI); MDR68_Male_RightAngle
R122, R124, R126, R128, R130, R132, R134, R136, R138, R140, R142, R144, R146, R148, R150, R152, R154, R156, R158, R160, R162, R164, R166, R168: 249; R_0603_1608Metric
R123, R125, R127, R129, R131, R133, R135, R137, R139, R141, R143, R145, R147, R149, R151, R153, R155, R157, R159, R161, R163, R165, R167, R169: 3.9k; R_0603_1608Metric
R170: 0; R_0603_1608Metric; not fitted
U56, U57, U58, U59, U60, U61: ACSL-6400-00TE; SOIC-16_3.9x9.9mm_P1.27mm
U62: TMA-0505S; Converter_DCDC_TRACO_TMA-05xxS_12xxS_Single_THT; not fitted

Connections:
BARCODE_BUF: U60.4 (CATHODE2); also elsewhere on the board
BARCODE_NI: J45.3, R157.2, U60.13 (VO2)
BARCODE_NI_LEDA: R156.2, U60.3 (ANODE2)
EVT_D0_BUF: U56.2 (CATHODE1); also elsewhere on the board
EVT_D0_NI: J45.52, R123.2, U56.14 (VO1)
EVT_D0_NI_LEDA: R122.2, U56.1 (ANODE1)
EVT_D1_BUF: U56.4 (CATHODE2); also elsewhere on the board
EVT_D1_NI: J45.17, R125.2, U56.13 (VO2)
EVT_D1_NI_LEDA: R124.2, U56.3 (ANODE2)
EVT_D2_BUF: U56.6 (CATHODE3); also elsewhere on the board
EVT_D2_NI: J45.49, R127.2, U56.12 (VO3)
EVT_D2_NI_LEDA: R126.2, U56.5 (ANODE3)
EVT_D3_BUF: U56.8 (CATHODE4); also elsewhere on the board
EVT_D3_NI: J45.47, R129.2, U56.11 (VO4)
EVT_D3_NI_LEDA: R128.2, U56.7 (ANODE4)
EVT_D4_BUF: U57.2 (CATHODE1); also elsewhere on the board
EVT_D4_NI: J45.19, R131.2, U57.14 (VO1)
EVT_D4_NI_LEDA: R130.2, U57.1 (ANODE1)
EVT_D5_BUF: U57.4 (CATHODE2); also elsewhere on the board
EVT_D5_NI: J45.51, R133.2, U57.13 (VO2)
EVT_D5_NI_LEDA: R132.2, U57.3 (ANODE2)
EVT_D6_BUF: U57.6 (CATHODE3); also elsewhere on the board
EVT_D6_NI: J45.16, R135.2, U57.12 (VO3)
EVT_D6_NI_LEDA: R134.2, U57.5 (ANODE3)
EVT_D7_BUF: U57.8 (CATHODE4); also elsewhere on the board
EVT_D7_NI: J45.48, R137.2, U57.11 (VO4)
EVT_D7_NI_LEDA: R136.2, U57.7 (ANODE4)
EVT_D8_BUF: U58.2 (CATHODE1); also elsewhere on the board
EVT_D8_NI: J45.11, R139.2, U58.14 (VO1)
EVT_D8_NI_LEDA: R138.2, U58.1 (ANODE1)
EVT_D9_BUF: U58.4 (CATHODE2); also elsewhere on the board
EVT_D9_NI: J45.10, R141.2, U58.13 (VO2)
EVT_D9_NI_LEDA: R140.2, U58.3 (ANODE2)
EVT_D10_BUF: U58.6 (CATHODE3); also elsewhere on the board
EVT_D10_NI: J45.43, R143.2, U58.12 (VO3)
EVT_D10_NI_LEDA: R142.2, U58.5 (ANODE3)
EVT_D11_BUF: U58.8 (CATHODE4); also elsewhere on the board
EVT_D11_NI: J45.42, R145.2, U58.11 (VO4)
EVT_D11_NI_LEDA: R144.2, U58.7 (ANODE4)
EVT_D12_BUF: U59.2 (CATHODE1); also elsewhere on the board
EVT_D12_NI: J45.41, R147.2, U59.14 (VO1)
EVT_D12_NI_LEDA: R146.2, U59.1 (ANODE1)
EVT_D13_BUF: U59.4 (CATHODE2); also elsewhere on the board
EVT_D13_NI: J45.6, R149.2, U59.13 (VO2)
EVT_D13_NI_LEDA: R148.2, U59.3 (ANODE2)
EVT_D14_BUF: U59.6 (CATHODE3); also elsewhere on the board
EVT_D14_NI: J45.5, R151.2, U59.12 (VO3)
EVT_D14_NI_LEDA: R150.2, U59.5 (ANODE3)
EVT_D15_BUF: U59.8 (CATHODE4); also elsewhere on the board
EVT_D15_NI: J45.38, R153.2, U59.11 (VO4)
EVT_D15_NI_LEDA: R152.2, U59.7 (ANODE4)
EVT_STROBE_BUF: U60.2 (CATHODE1); also elsewhere on the board
EVT_STROBE_NI: J45.37, R155.2, U60.14 (VO1)
EVT_STROBE_NI_LEDA: R154.2, U60.1 (ANODE1)
NI_5V: C121.1, C122.1, C123.1, C124.1, C125.1, C126.1, C127.1, C128.1, C129.1, C130.1, C131.1, C132.1, C133.1, C134.1, J45.8, J45.14, R123.1, R125.1, R127.1, R129.1, R131.1, R133.1, R135.1, R137.1, R139.1, R141.1, R143.1, R145.1, R147.1, R149.1, R151.1, R153.1, R155.1, R157.1, R159.1, R161.1, R163.1, R165.1, R167.1, R169.1, R170.2, U56.10 (VDD), U56.15 (VDD), U57.10 (VDD), U57.15 (VDD), U58.10 (VDD), U58.15 (VDD), U59.10 (VDD), U59.15 (VDD), U60.10 (VDD), U60.15 (VDD), U61.10 (VDD), U61.15 (VDD)
NI_5V_FB_FILT: C136.1, FB3.2, R170.1
NI_5V_FB_RAW: C135.1, FB3.1, U62.6 (+Vout)
NI_GND: C121.2, C122.2, C123.2, C124.2, C125.2, C126.2, C127.2, C128.2, C129.2, C130.2, C131.2, C132.2, C133.2, C134.2, C135.2, C136.2, J45.4, J45.7, J45.9, J45.12, J45.13, J45.15, J45.18, J45.35, J45.36, J45.44, J45.50, J45.53, U56.9 (GND), U56.16 (GND), U57.9 (GND), U57.16 (GND), U58.9 (GND), U58.16 (GND), U59.9 (GND), U59.16 (GND), U60.9 (GND), U60.16 (GND), U61.9 (GND), U61.16 (GND), U62.4 (-Vout)
PD1_COMP_BUF: U61.6 (CATHODE3); also elsewhere on the board
PD1_COMP_NI: J45.1, R167.2, U61.12 (VO3)
PD1_COMP_NI_LEDA: R166.2, U61.5 (ANODE3)
PD2_COMP_BUF: U61.8 (CATHODE4); also elsewhere on the board
PD2_COMP_NI: J45.39, R169.2, U61.11 (VO4)
PD2_COMP_NI_LEDA: R168.2, U61.7 (ANODE4)
RHS_STIM_OUT_BUF: U61.4 (CATHODE2); also elsewhere on the board
RHS_STIM_OUT_NI: J45.40, R165.2, U61.13 (VO2)
RHS_STIM_OUT_NI_LEDA: R164.2, U61.3 (ANODE2)
RWD_CMD_BUF: U60.6 (CATHODE3); also elsewhere on the board
RWD_CMD_NI: J45.45, R159.2, U60.12 (VO3)
RWD_CMD_NI_LEDA: R158.2, U60.5 (ANODE3)
RWD_DLVR_BUF: U60.8 (CATHODE4); also elsewhere on the board
RWD_DLVR_NI: J45.46, R161.2, U60.11 (VO4)
RWD_DLVR_NI_LEDA: R160.2, U60.7 (ANODE4)
STIM_TRIG_BUF: U61.2 (CATHODE1); also elsewhere on the board
STIM_TRIG_NI: J45.2, R163.2, U61.14 (VO1)
STIM_TRIG_NI_LEDA: R162.2, U61.1 (ANODE1)

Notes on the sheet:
Opto-NI (Task 11) -- 24 digital channels, DGND domain -> NI-isolated domain,
via six Broadcom ACSL-6400 (quad, all-in-one, 15 MBd logic-output optocoupler,
16-pin SOIC -- NOT phototransistor, matching the mule's own validated part
class). Also places the recording NI's own Connector 1 (digital) -- Connector 0
(analog) was already placed by Task 10b on analog-ni.kicad_sch; not duplicated.
Channels: EVT_D0_BUF..EVT_D15_BUF (16), EVT_STROBE_BUF, BARCODE_PI, RWD_CMD_BUF,
RWD_DLVR, STIM_TRIG_BUF, RHS_STIM_OUT, PD1_COMP, PD2_COMP -- 24 total, filling
Connector 1's own P0.8-P0.31 exactly, no spares on this side (all this domain's
own spare headroom lives on opto-intan's own second package).
TOPOLOGY IS NON-INVERTING, unlike the mule's own drive orientation -- see this
generator's own module docstring for the full derivation. +5V -> R_LED -> ANODE;
CATHODE -> source_net. source_net HIGH -> LED off -> isolated output HIGH;
source_net LOW -> LED on -> isolated output LOW. Relies only on the driving
74HCT541/74HCT32 push-pull output's ordinary ability to sink a few mA -- standard
practice, not a special requirement.
LED DRIVE: 249R (E96, 1%) -- FINDING F1, 2026-08-16. Was 430R, which
under-drove all 24 of these LEDs: ~5mA worst case against the ACSL-6xx0's own
7.0mA I_FH minimum, i.e. not guaranteed to switch at all. The original sizing
was arithmetically right and physically wrong -- it solved (5.0V - VOL - VF)/I
using the rail's NOMINAL 5.00V and VF TYP (1.52V), but +5V reaches these anodes
through F4 and D3 (0.38-0.45V of drop, so 4.55-4.62V) and VF's worst case is
1.80V. 249R gives 8.6mA worst / 13.7mA best: clear of the 8mA guardbanded floor
(AV02-0235EN footnote b) and of the 15mA ABSOLUTE maximum. 240R was rejected at
99% of that maximum; 270R misses the 8mA floor.
THIS VALUE IS ONLY SAFE PARALLELED: at 249R one LED draws ~12.7mA, over a
single SN74AHCT541 output's 7.5mA budget, so every LED here is driven by TWO
outputs from tied inputs (taskpc-digital's U70-U73). It also assumes the
external +5V supply is specified at +-2% -- at +-5% the tolerance spread is
1.95:1 against a 2.14:1 window, which fits with nothing to spare. That
tolerance is a load-bearing specification now, not an assumption.
NI-SIDE PULL-UP: 3.9k -- fix round 1, corrected from this task's original 10k,
which compared only against the mule's own 1k and never checked ACSL-6400's
own datasheet RL-max (4k); 10k exceeded it. 3.9k (E24) is the largest E24 value
at or under that limit. 24 stages at ~5-7mA (IDDL) draw 120-168mA against NI's
250mA budget; 3.9k pull-ups add ~31mA (domain total 151-199mA, 51-99mA
headroom) -- 10k added only ~12mA, but only by violating the part's own spec.
Logic-level integrity holds (worst-case VOH >= NI_5V-0.39V at the datasheet's
own worst-case leakage; VOL only improves at the lighter sink current); edge
rate (tau~0.2us into ~50pF) was never close enough to the 500us strobe to
decide this either way -- see the module docstring for the full derivation.
